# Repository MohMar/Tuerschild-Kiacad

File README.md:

# Tuerschild-Kiacad
aktuelle Projekt Türschilder

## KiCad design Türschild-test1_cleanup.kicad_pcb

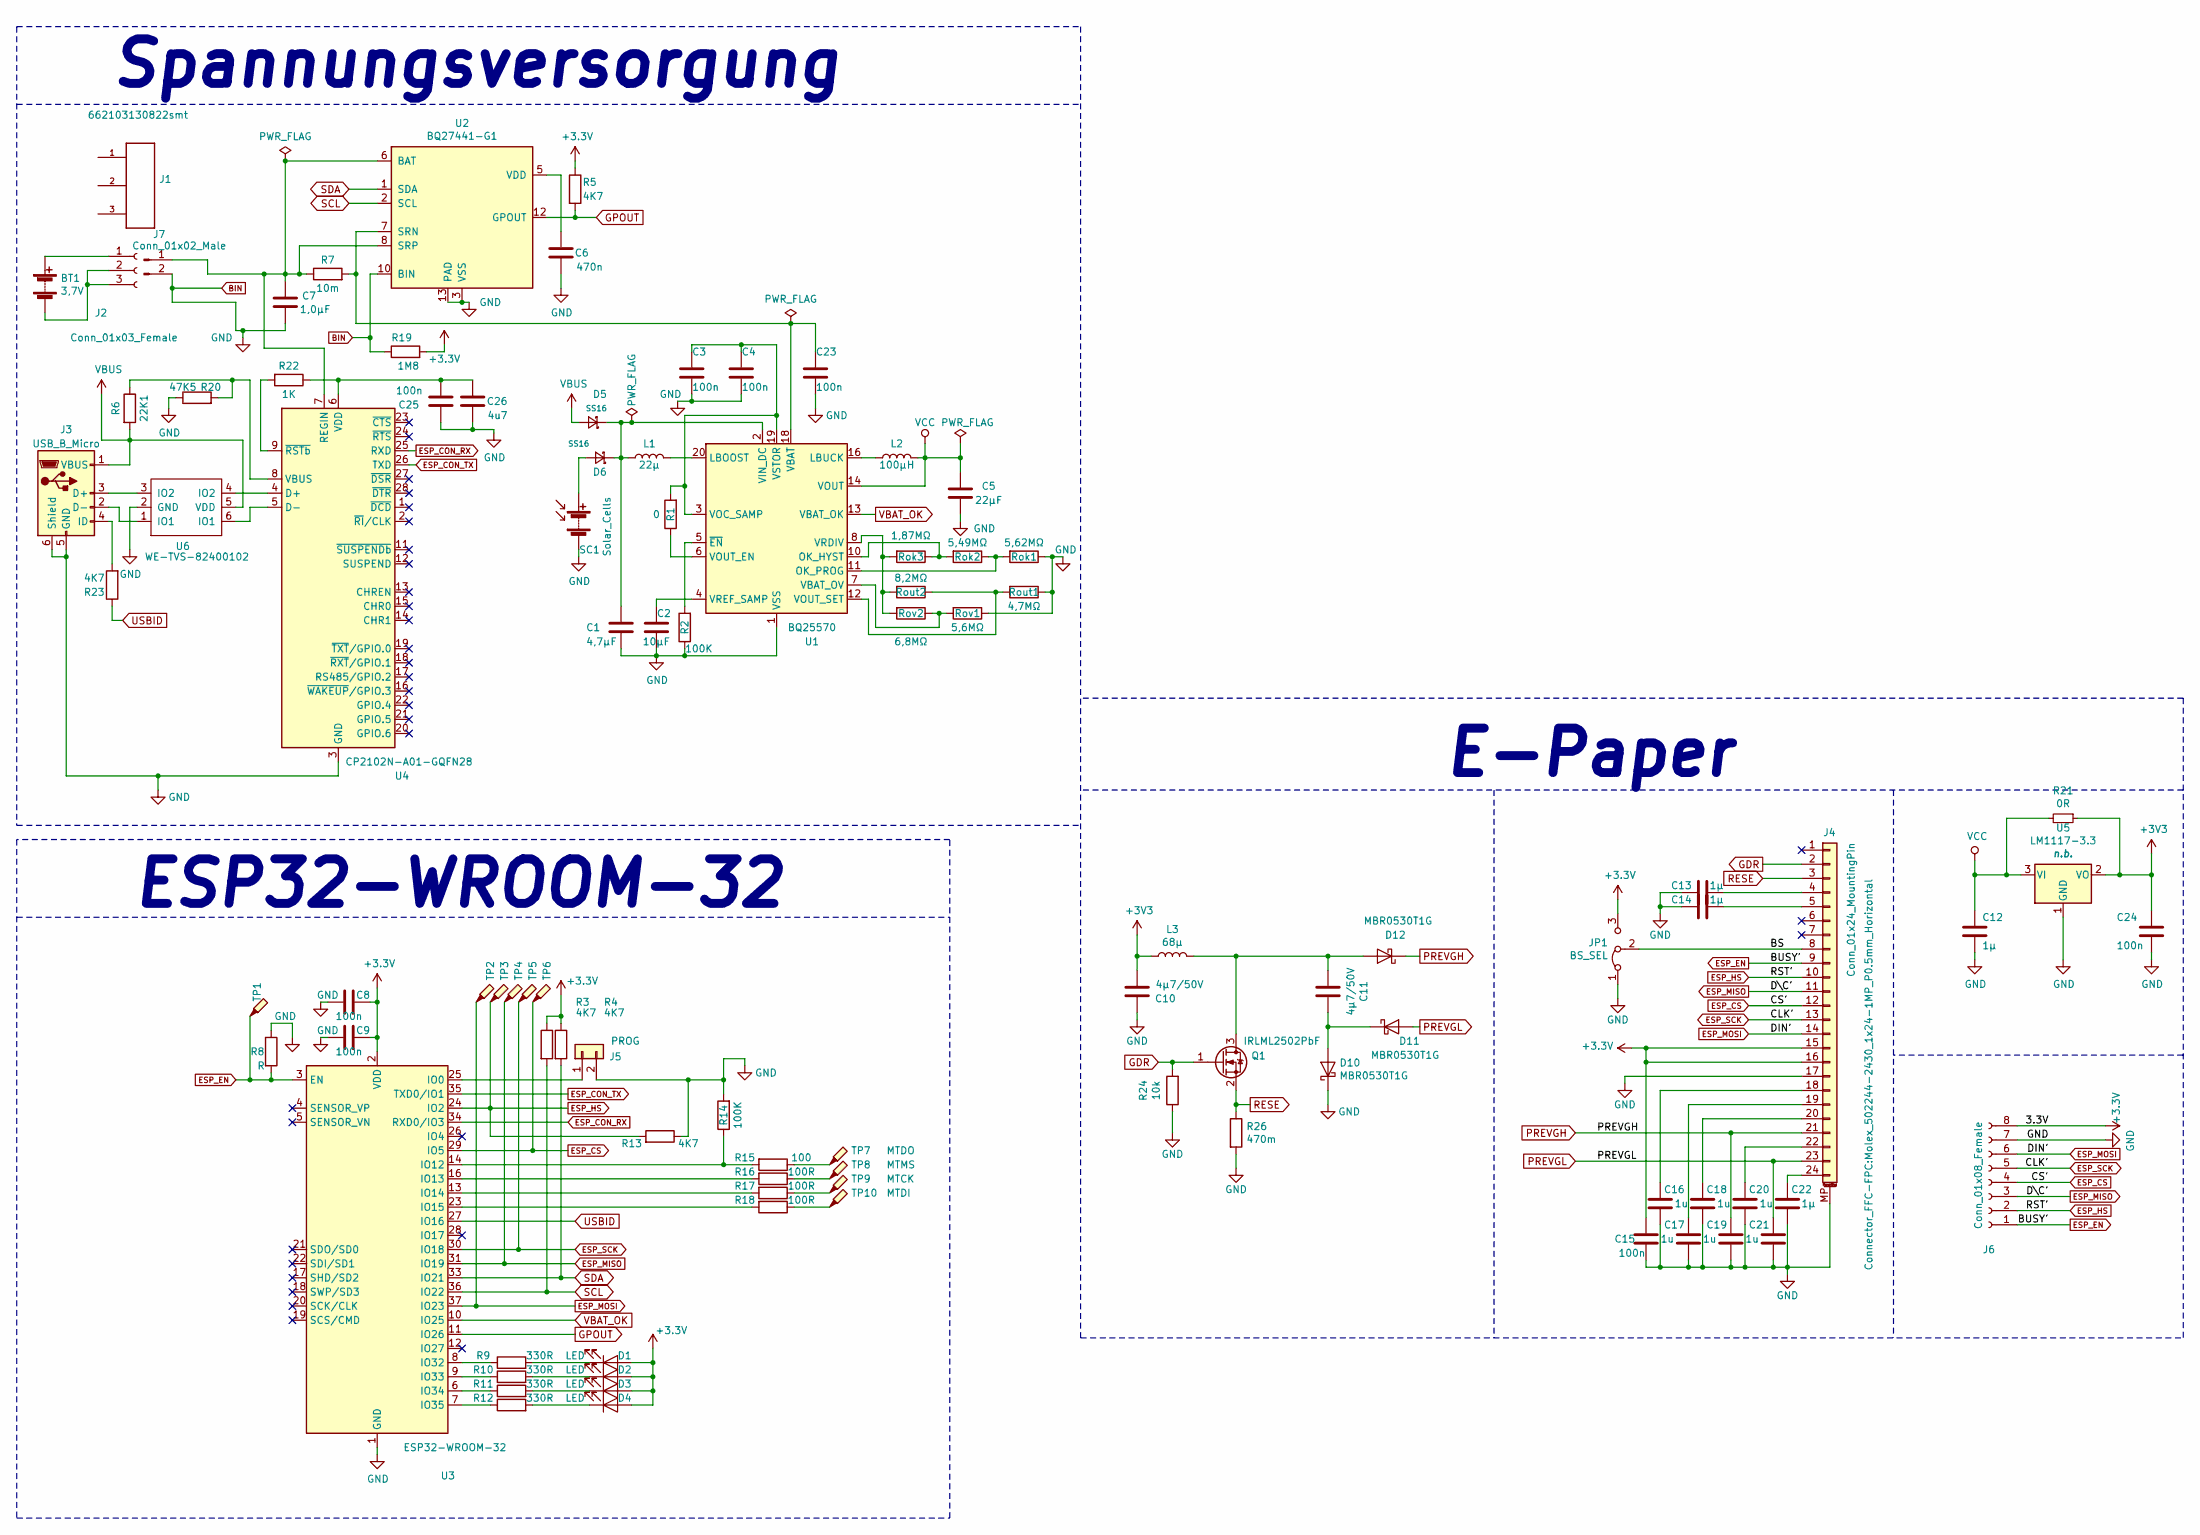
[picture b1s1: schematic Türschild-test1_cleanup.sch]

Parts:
BT1: 3,7V; BatteryHolder_Bulgin_BX0036_1xC
C1: 4,7µF; C_0805_2012Metric_Pad1.15x1.40mm_HandSolder
C2: 10µF; C_0805_2012Metric_Pad1.15x1.40mm_HandSolder
C3, C4, C8, C9, C15, C23, C24, C25: 100n; C_0603_1608Metric_Pad1.05x0.95mm_HandSolder
C5: 22µF; C_0603_1608Metric_Pad1.05x0.95mm_HandSolder
C6: 470n; C_0603_1608Metric_Pad1.05x0.95mm_HandSolder
C7: 1,0µF; C_0603_1608Metric_Pad1.05x0.95mm_HandSolder
C10, C11: 4µ7/50V; C_0805_2012Metric_Pad1.15x1.40mm_HandSolder
C12, C13, C14, C22: 1µ; C_0603_1608Metric_Pad1.05x0.95mm_HandSolder
C16, C17, C18, C19, C20, C21: 1u; C_0603_1608Metric_Pad1.05x0.95mm_HandSolder
C26: 4u7; C_0805_2012Metric_Pad1.15x1.40mm_HandSolder
D1, D2, D3, D4: LED; LED_0603_1608Metric_Pad1.05x0.95mm_HandSolder
D5, D6: SS16; D_SMA-SMB_Universal_Handsoldering
D10, D11, D12: MBR0530T1G; D_SOD-123
J1: 662103130822smt; Molex_PicoBlade_53047-0310_1x03_P1.25mm_Vertical
J2: Conn_01x03_Female; PinSocket_1x03_P2.00mm_Vertical_SMD_Pin1Right
J3: USB_B_Micro; USB_Mini-B_Wuerth_65100516121_Horizontal
J4: Conn_01x24_MountingPin; Molex_502244-2430_1x24-1MP_P0.5mm_Horizontal
J5: PROG; SolderJumper-2_P1.3mm_Bridged_Pad1.0x1.5mm
J6: Conn_01x08_Female; PinHeader_1x08_P1.00mm_Horizontal
J7: Conn_01x02_Male; Molex_PicoBlade_53047-0210_1x02_P1.25mm_Vertical
JP1: BS_SEL; SolderJumper-3_P1.3mm_Bridged12_Pad1.0x1.5mm_NumberLabels
L1: 22µ; L_Wuerth_WE-TPC-3816
L2: 100µH; L_Wuerth_WE-TPC-3816
L3: 68µ; L_Wuerth_WE-TPC-3816
Q1: IRLML2502PbF; SOT-23
R1: 0; R_0603_1608Metric_Pad1.05x0.95mm_HandSolder
R2, R14: 100K; R_0603_1608Metric_Pad1.05x0.95mm_HandSolder
R3, R4, R5, R13, R23: 4K7; R_0603_1608Metric_Pad1.05x0.95mm_HandSolder
R6: 22K1; R_0603_1608Metric_Pad1.05x0.95mm_HandSolder
R7: 10m; R_0603_1608Metric_Pad1.05x0.95mm_HandSolder
R8: R; R_0603_1608Metric_Pad1.05x0.95mm_HandSolder
R9, R10, R11, R12: 330R; R_0603_1608Metric_Pad1.05x0.95mm_HandSolder
R15: 100; R_0603_1608Metric_Pad1.05x0.95mm_HandSolder
R16, R17, R18: 100R; R_0603_1608Metric_Pad1.05x0.95mm_HandSolder
R19: 1M8; R_0603_1608Metric_Pad1.05x0.95mm_HandSolder
R20: 47K5; R_0603_1608Metric_Pad1.05x0.95mm_HandSolder
R21: 0R; R_0603_1608Metric_Pad1.05x0.95mm_HandSolder
R22: 1K; R_0603_1608Metric_Pad1.05x0.95mm_HandSolder
R24: 10k; R_0603_1608Metric_Pad1.05x0.95mm_HandSolder
R26: 470m; R_0603_1608Metric_Pad1.05x0.95mm_HandSolder
Rok1: 5,62МΩ; R_0603_1608Metric_Pad1.05x0.95mm_HandSolder
Rok2: 5,49МΩ; R_0603_1608Metric_Pad1.05x0.95mm_HandSolder
Rok3: 1,87МΩ; R_0603_1608Metric_Pad1.05x0.95mm_HandSolder
Rout1: 4,7МΩ; R_0603_1608Metric_Pad1.05x0.95mm_HandSolder
Rout2: 8,2МΩ; R_0603_1608Metric_Pad1.05x0.95mm_HandSolder
Rov1: 5,6МΩ; R_0603_1608Metric_Pad1.05x0.95mm_HandSolder
Rov2: 6,8МΩ; R_0603_1608Metric_Pad1.05x0.95mm_HandSolder
SC1: Solar_Cells; PinHeader_1x02_P2.54mm_Horizontal
TP1, TP2, TP3, TP4, TP5, TP6: TestPoint_Probe; TestPoint_Pad_1.0x1.0mm
TP7: MTDO; TestPoint_Pad_1.0x1.0mm
TP8: MTMS; TestPoint_Pad_1.0x1.0mm
TP9: MTCK; TestPoint_Pad_1.0x1.0mm
TP10: MTDI; TestPoint_Pad_1.0x1.0mm
U1: BQ25570; QFN-20-1EP_3.5x3.5mm_P0.5mm_EP2x2mm
U2: BQ27441-G1; Texas_S-PDSO-N12
U3: ESP32-WROOM-32
U4: CP2102N-A01-GQFN28; QFN-28-1EP_5x5mm_P0.5mm_EP3.35x3.35mm
U5: LM1117-3.3; SOT-223-3_TabPin2
U6: WE-TVS-82400102; SOT-23-6_Handsoldering

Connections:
/BS: J4.8, JP1.2 (C)
BIN: C1.2, C2.2, C3.2, C4.2, C5.1, C6.1, C7.2, C8.2, C9.2, C10.1, C12.2, C13.2, C14.2, C15.1, C16.1, C17.1, C18.1, C19.1, C20.1, C21.1, C22.1, C23.2, C24.2, C25.2, C26.2, D10.1 (K), J3.5 (GND), J3.6 (Shield), J4.17, J4.MP (MountPin), J5.2, J6.7, J7.2, JP1.1 (A), R2.1, R8.1, R13.1, R14.2, R19.1, R20.1, R24.1, R26.2, Rok1.1, Rout1.1, Rov1.1, SC1.2 (-), U1.1 (VSS), U1.9 (VSS), U1.15 (VSS), U1.17 (VSS), U1.21 (VSS), U2.3 (VSS), U2.10 (BIN), U2.13 (PAD), U3.1 (GND), U3.15 (GND), U3.38 (GND), U3.39 (GND), U4.3 (GND), U4.29 (GND), U5.1 (GND), U6.2 (GND)
ESP_CON_RX: U3.34 (RXD0/IO3), U4.25 (RXD)
ESP_CON_TX: U3.35 (TXD0/IO1), U4.26 (TXD)
ESP_CS: J4.12, J6.4, TP6.1, U3.29 (IO5)
ESP_EN: J4.9, J6.1, R8.2, TP1.1, U3.3 (EN)
ESP_HS: J4.10, J6.2, R13.2, TP3.1, U3.24 (IO2)
ESP_MISO: J4.11, J6.3, TP4.1, U3.31 (IO19)
ESP_MOSI: J4.14, J6.6, TP2.1, U3.37 (IO23)
ESP_SCK: J4.13, J6.5, TP5.1, U3.30 (IO18)
GDR: J4.2, Q1.1 (G), R24.2
GPOUT: R5.2, U2.12 (GPOUT), U3.11 (IO26)
unnamed: BT1.1 (+), J2.1
unnamed: BT1.2 (-), J2.2, J2.3
unnamed: C1.1, D5.1 (K), D6.1 (K), L1.1, U1.2 (VIN_DC)
unnamed: C2.1, U1.4 (VREF_SAMP)
unnamed: C3.1, C4.1, R1.2, U1.3 (VOC_SAMP), U1.19 (VSTOR)
unnamed: C6.2, U2.5 (VDD)
unnamed: C7.1, J7.1, R7.1, U2.6 (BAT), U2.8 (SRP), U4.7 (REGIN)
unnamed: C11.1, D10.2 (A), D11.1 (K)
unnamed: C11.2, D12.2 (A), L3.2, Q1.3 (D)
unnamed: C13.1, J4.4
unnamed: C14.1, J4.5
unnamed: C16.2, J4.18
unnamed: C17.2, J4.19
unnamed: C18.2, J4.20
unnamed: C20.2, J4.22
unnamed: C22.2, J4.24
unnamed: C23.1, R7.2, U1.18 (VBAT), U2.7 (SRN)
unnamed: C25.1, C26.1, R22.1, U4.6 (VDD)
unnamed: D1.1 (K), R9.2
unnamed: D2.1 (K), R10.2
unnamed: D3.1 (K), R11.2
unnamed: D4.1 (K), R12.2
unnamed: D6.2 (A), SC1.1 (+)
unnamed: J3.2 (D-), U6.1 (IO1)
unnamed: J3.3 (D+), U6.3 (IO2)
unnamed: J3.4 (ID), R23.2
unnamed: J5.1, U3.25 (IO0)
unnamed: L1.2, U1.20 (LBOOST)
unnamed: L2.1, U1.16 (LBUCK)
unnamed: R1.1, U1.6 (VOUT_EN)
unnamed: R2.2, U1.5 (~EN)
unnamed: R9.1, U3.8 (IO32)
unnamed: R10.1, U3.9 (IO33)
unnamed: R11.1, U3.6 (IO34)
unnamed: R12.1, U3.7 (IO35)
unnamed: R14.1, R15.2, U3.14 (IO12)
unnamed: R15.1, TP7.1
unnamed: R16.1, TP8.1
unnamed: R16.2, U3.16 (IO13)
unnamed: R17.1, TP9.1
unnamed: R17.2, U3.13 (IO14)
unnamed: R18.1, TP10.1
unnamed: R18.2, U3.23 (IO15)
unnamed: R6.1, R20.2, U4.8 (VBUS)
unnamed: R22.2, U4.9 (~RSTb)
unnamed: Rok1.2, Rok2.1, U1.11 (OK_PROG)
unnamed: Rok2.2, Rok3.1, U1.10 (OK_HYST)
unnamed: Rok3.2, Rout2.2, Rov2.2, U1.8 (VRDIV)
unnamed: Rout1.2, Rout2.1, U1.12 (VOUT_SET)
unnamed: Rov1.2, Rov2.1, U1.7 (VBAT_OV)
unnamed: U4.4 (D+), U6.4 (IO2)
unnamed: U4.5 (D-), U6.6 (IO1)
PREVGH: C19.2, D12.1 (K), J4.21
PREVGL: C21.2, D11.2 (A), J4.23
RESE: J4.3, Q1.2 (S), R26.1
SCL: R3.2, U2.2 (SCL), U3.36 (IO22)
SDA: R4.2, U2.1 (SDA), U3.33 (IO21)
USBID: R23.1, U3.27 (IO16)
VBAT_OK: U1.13 (VBAT_OK), U3.10 (IO25)
VBUS: D5.2 (A), J3.1 (VBUS), R6.2, U6.5 (VDD)
VCC: C5.2, C12.1, L2.2, R21.2, U1.14 (VOUT), U5.3 (VI)

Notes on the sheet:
E-Paper
Spannungsversorgung
ESP32-WROOM-32

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
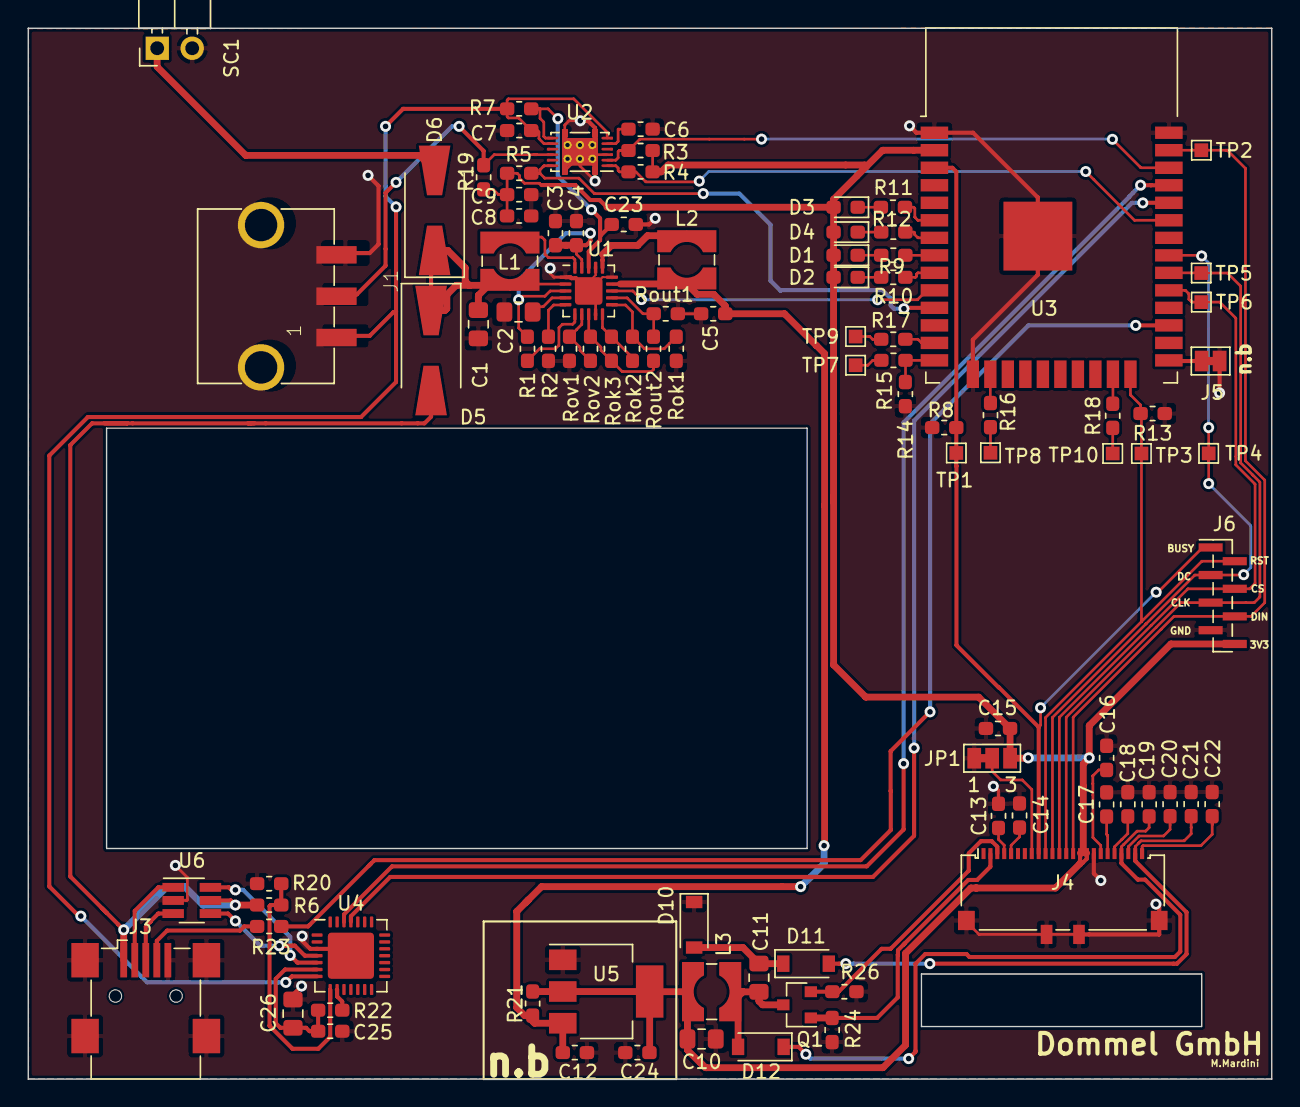
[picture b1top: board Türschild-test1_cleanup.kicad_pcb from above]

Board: 2 copper layers, 90.2 x 76.2 mm, 94 parts (0 on the bottom side), 72 nets.

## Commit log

2020-04-15 HowTo Changes mit Daniel
2020-04-15 Added 3D-Model
2020-05-08 Version 1
2020-06-04 layout verbessert
2020-08-13 Akkustecker hinzugefügt layout verbessert
2020-10-28 Plotten
2021-03-03 Pull-Ups und Pull-Downs für die beiden USB-Datenleitungen eingebaut. nur 1K5 Wiederstand auf D+ gegen 3V3 wurde bestückt
    neue Schaltplan und Layout für korrektour erstellt
